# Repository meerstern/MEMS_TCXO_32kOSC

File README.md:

# 32.768kHz温度補償型MEMS発振器
MEMS TCXO 32.768kHz Oscillator for RTC

## 概要 
  * SiTime製温度補償型32.768kHzMEMS発振器のブレイクアウト基板です 
  * [SIT1552AC-JE-DCC-32.768][1]を2.54mmピッチに変換しています  
  * ±5ppmの高精度を実現しています
  * RTCの水晶発振子を置き換えることで経時の時刻ずれを低減することが可能です  
  * 一般的な±30ppmの水晶発振子で1年間15分前後のずれを数分程度まで低減させることが可能です  
  * マイコン内蔵のRTCや温度補償機能のないRTCの高精度化に最適です  
  * LVCMOS出力のため、配線長による負荷容量の影響を受けにくく、設計自由度が向上します  
  * 990nAの超低消費電力のため、RTC電池での運用も可能です  
  * ピン名V:電源、C:クロック出力(LVCMOS)、G:GND  
  * 基板サイズ10mm x10mm
  * 電源1.5~3.63V
  
## 注意事項
  * 発振器は1.5mm x0.8mmの超小型CSPのため、取り扱いに注意してください  
  * 衝撃や外力を与えると発振器の破損やハンダボールのクラック原因になります  
  * 発振器内にパスコンを内蔵しているため、外付けのパスコンは未実装となっています  
  * 水晶発振子の代わりに使用する際はXINにクロック出力を接続、XOUTは未接続にしてください  
  * 電源はバックアップ時も供給できるように電池等の電源に接続してください  
  * 各マイコンの設定方法については[こちらのPDF][2]を参照してください
  * 出荷前に全数のクロック出力を確認しています  

  MIT Lisense
  
  [1]: https://www.sitime.com/products/32-khz-tcxos/sit1552
  [2]: https://www.sitime.com/api/gated/AN10037-SiT15xx-Optimized-Settings-for-32kHz-Inputs-MCUs.pdf

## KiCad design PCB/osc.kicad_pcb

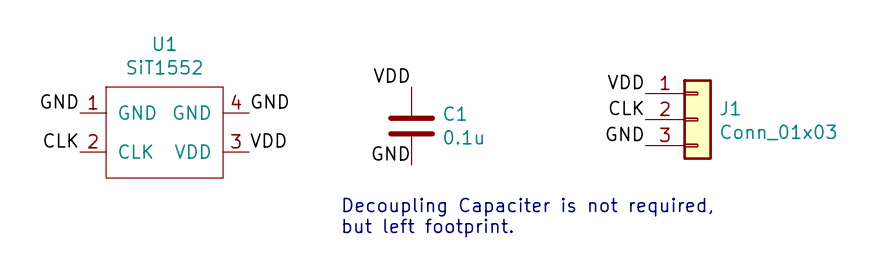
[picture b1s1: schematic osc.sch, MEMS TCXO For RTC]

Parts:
C1: 0.1u; C_0603_1608Metric
J1: Conn_01x03; PinHeader_1x03_P2.54mm_Vertical
U1: SiT1552

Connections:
/CLK: J1.2, U1.2 (CLK)
/GND: C1.2, J1.3, U1.1 (GND), U1.4 (GND)
/VDD: C1.1, J1.1, U1.3 (VDD)

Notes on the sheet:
Decoupling Capaciter is not required, but left footprint.

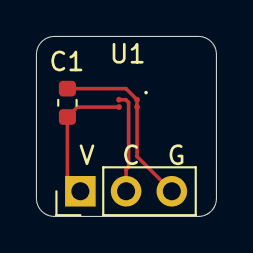
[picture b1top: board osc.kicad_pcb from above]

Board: 2 copper layers, 10.0 x 10.0 mm, 3 parts (0 on the bottom side), 3 nets.

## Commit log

2023-03-04 Add pcb files
2023-03-04 Add images
